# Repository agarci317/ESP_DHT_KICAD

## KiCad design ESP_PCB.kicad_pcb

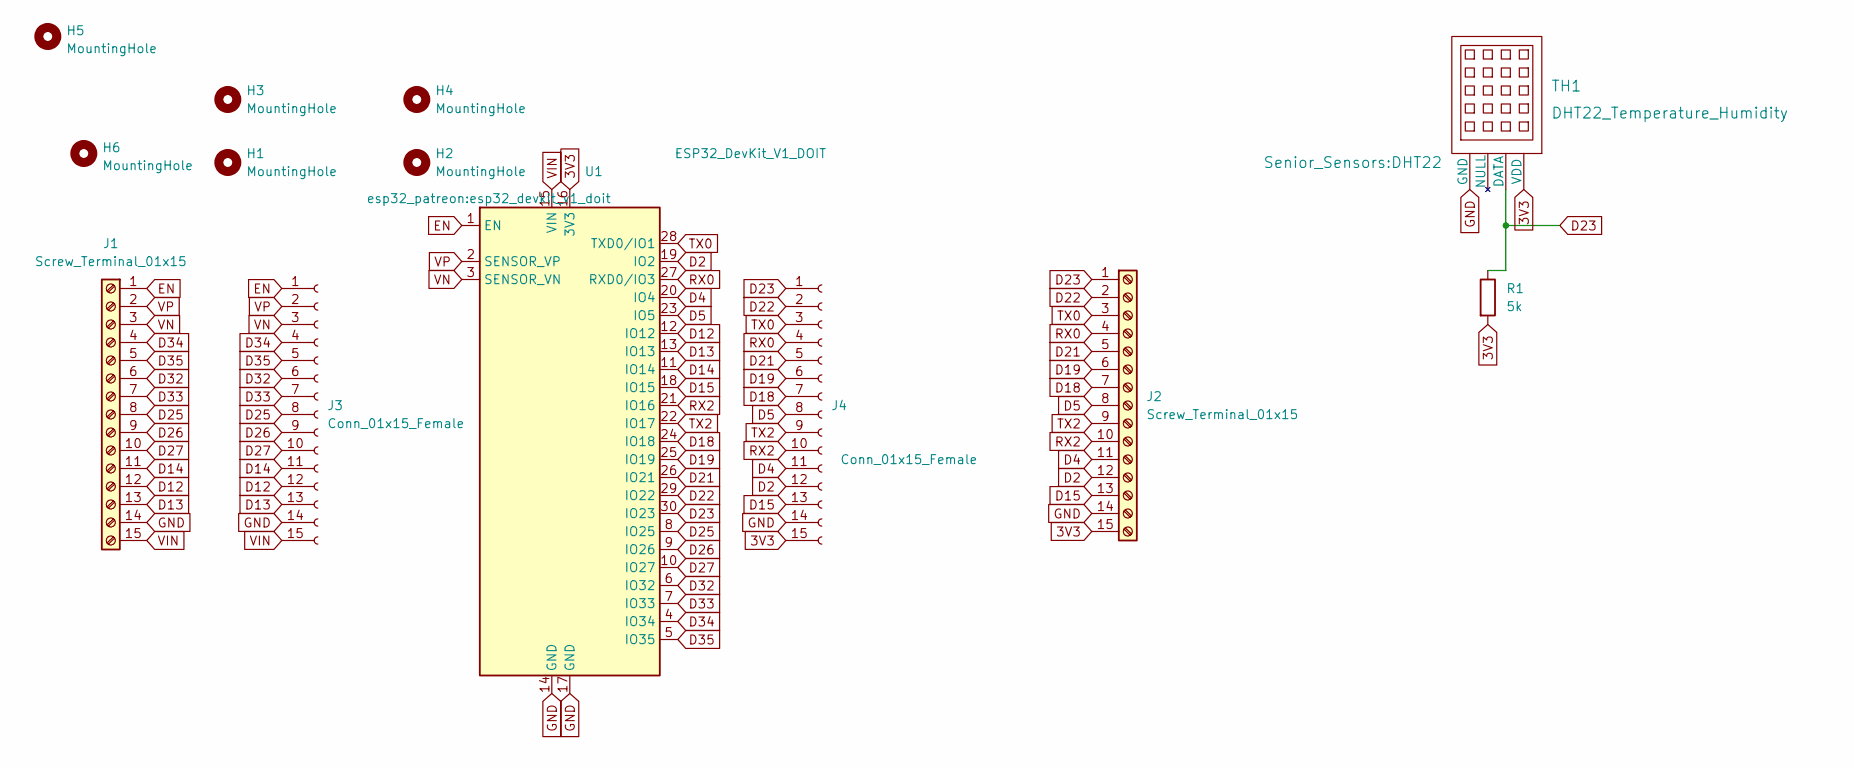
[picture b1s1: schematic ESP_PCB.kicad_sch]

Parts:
H1, H2, H3, H4, H5, H6: MountingHole; MountingHole_2.5mm
J1, J2: Screw_Terminal_01x15; PhoenixContact_MSTBV_2,5_15-GF_1x15_P5.00mm_Vertical_Thread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
J3: Conn_01x15_Female; PinSocket_1x15_P2.54mm_Vertical
J4: Conn_01x15_Female; PhoenixContact_MCV_1,5_11-G-5.08_1x11_P5.08mm_Vertical
R1: 5k; R_Axial_DIN0204_L3.6mm_D1.6mm_P7.62mm_Horizontal
TH1: DHT22_Temperature_Humidity; DHT22
U1: ESP32_DevKit_V1_DOIT; esp32_devkit_v1_doit

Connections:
3V3: J2.15, J4.15, R1.2, TH1.1 (VDD), U1.16 (3V3)
D2: J2.12, J4.12, U1.19 (IO2)
D4: J2.11, J4.11, U1.20 (IO4)
D5: J2.8, J4.8, U1.23 (IO5)
D12: J1.12, J3.12, U1.12 (IO12)
D13: J1.13, J3.13, U1.13 (IO13)
D14: J1.11, J3.11, U1.11 (IO14)
D15: J2.13, J4.13, U1.18 (IO15)
D18: J2.7, J4.7, U1.24 (IO18)
D19: J2.6, J4.6, U1.25 (IO19)
D21: J2.5, J4.5, U1.26 (IO21)
D22: J2.2, J4.2, U1.29 (IO22)
D23: J2.1, J4.1, R1.1, TH1.2 (DATA), U1.30 (IO23)
D25: J1.8, J3.8, U1.8 (IO25)
D26: J1.9, J3.9, U1.9 (IO26)
D27: J1.10, J3.10, U1.10 (IO27)
D32: J1.6, J3.6, U1.6 (IO32)
D33: J1.7, J3.7, U1.7 (IO33)
D34: J1.4, J3.4, U1.4 (IO34)
D35: J1.5, J3.5, U1.5 (IO35)
EN: J1.1, J3.1, U1.1 (EN)
GND: J1.14, J2.14, J3.14, J4.14, TH1.4 (GND), U1.14 (GND), U1.17 (GND)
RX0: J2.4, J4.4, U1.27 (RXD0/IO3)
RX2: J2.10, J4.10, U1.21 (IO16)
TX0: J2.3, J4.3, U1.28 (TXD0/IO1)
TX2: J2.9, J4.9, U1.22 (IO17)
VIN: J1.15, J3.15, U1.15 (VIN)
VN: J1.3, J3.3, U1.3 (SENSOR_VN)
VP: J1.2, J3.2, U1.2 (SENSOR_VP)

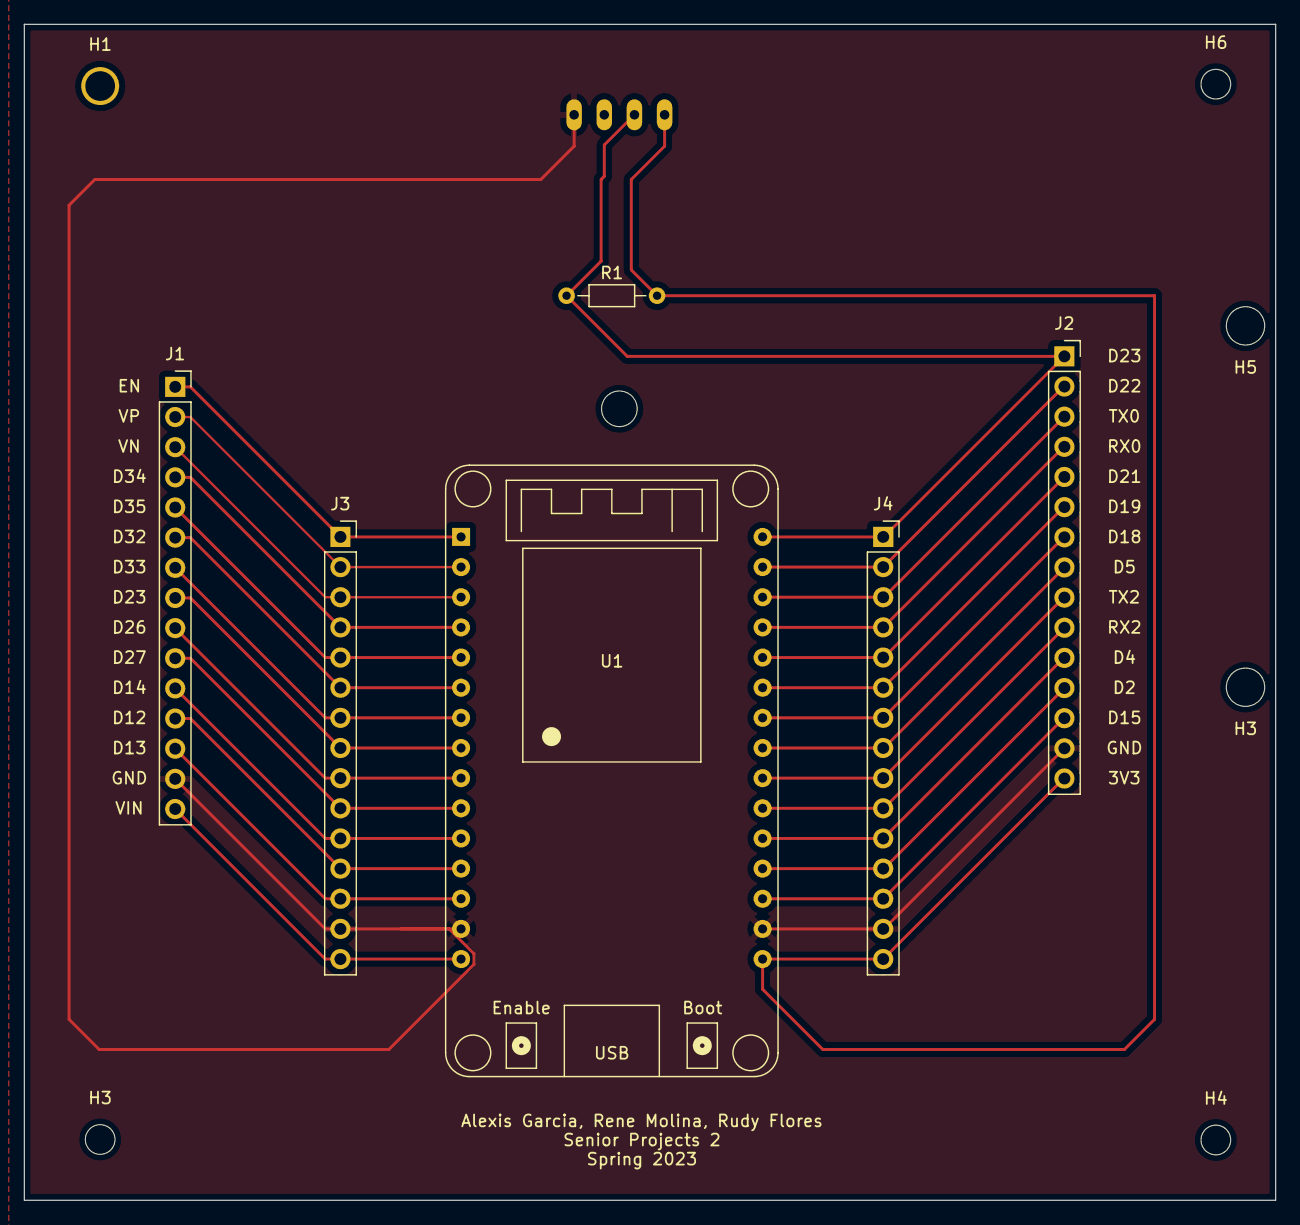
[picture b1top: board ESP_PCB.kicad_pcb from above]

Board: 2 copper layers, 105.4 x 99.1 mm, 13 parts (1 on the bottom side), 29 nets.

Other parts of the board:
H3#2: MountingHole; MountingHole_2.5mm
